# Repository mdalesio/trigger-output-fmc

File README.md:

# Trigger Output FMC

A single width HPC FMC board which provides 16 low jitter TTL outputs,
along with two Si5394 jitter cleaners with outputs connected to the MGTREF capable
when matched with the [LBL Marble](https://github.com/BerkeleyLab/Marble) FMC carrier.

This design is Open Hardware created by Osprey DCS and published under the terms of the
[CERN Open Hardware Licence Version 2 - Strongly Reciprocal](cern_ohl_s_v2.txt) license.

This repository contains KiCad 9.0.4 design files.

- [Data sheet](datasheet.md)
- [Current generated](https://osprey-dcs.github.io/trigger-output-fmc/)
  - [Schematic](https://osprey-dcs.github.io/trigger-output-fmc/trigger-output-fmc-schematic.pdf)
  - [BoM](https://osprey-dcs.github.io/trigger-output-fmc/trigger-output-fmc-bom.csv)
  - [STeP model](https://osprey-dcs.github.io/trigger-output-fmc/3D/trigger-output-fmc-3D.step)

## Block Diagram

## Status

Revision 1.0 produced and tested.

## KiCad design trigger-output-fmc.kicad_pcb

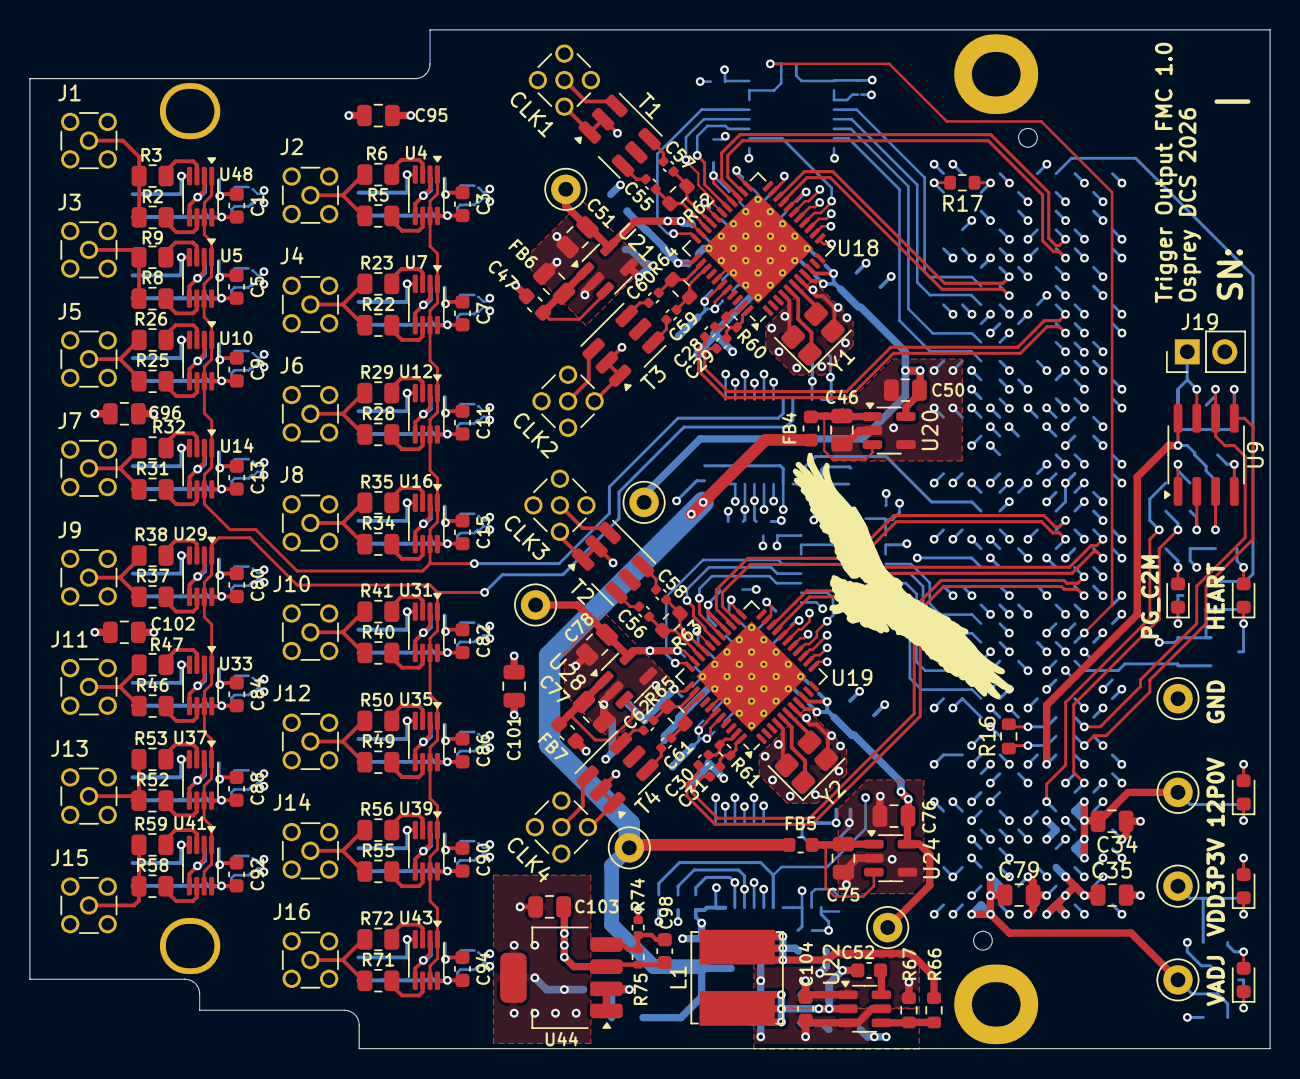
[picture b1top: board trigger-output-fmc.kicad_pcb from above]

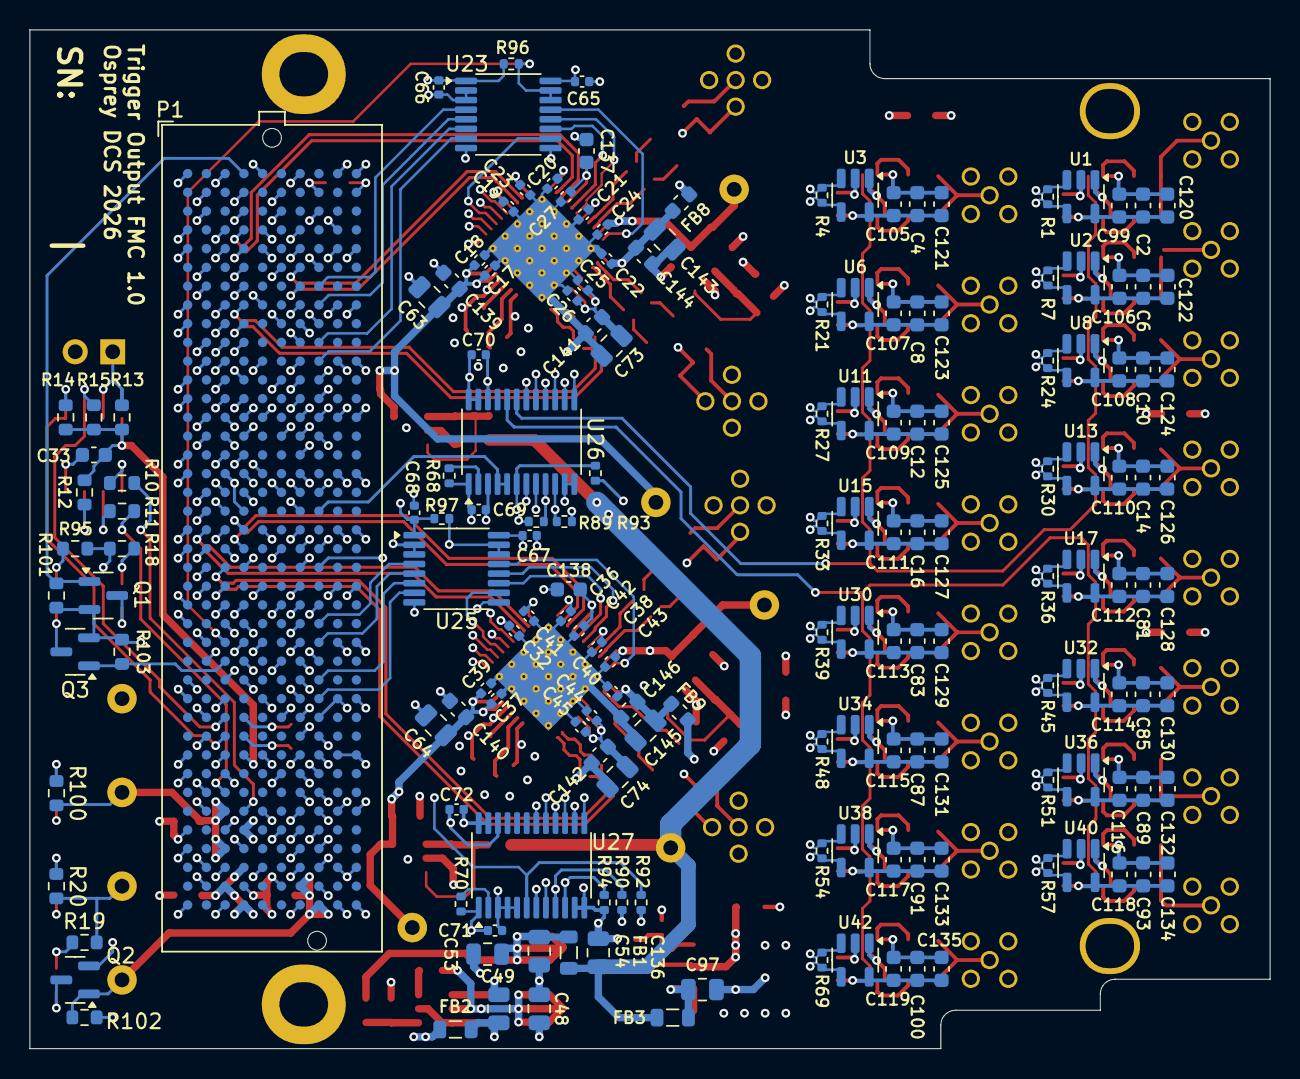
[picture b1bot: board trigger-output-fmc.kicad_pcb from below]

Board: 8 copper layers, 84.0 x 69.0 mm, 335 parts (168 on the bottom side), 226 nets.

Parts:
C1, C2, C3, C4, C5, C6, C7, C8, C9, C10, C11, C12, C13, C14, C15, C16, C52, C80, C81, C82, C83, C84, C85, C86, C87, C88, C89, C90, C91, C92, C93, C94, C100, C104: 100nF; C_0603_1608Metric
C17, C18, C19, C20, C21, C22, C23, C24, C25, C26, C27, C28, C29, C30, C31, C32, C36, C37, C38, C39, C40, C41, C42, C43, C44, C45, C55, C56, C57, C58, C59, C60, C61, C62, C65, C66, C67, C68, C69, C70, C71, C72: 100nF; C_0402_1005Metric
C33, C120, C121, C122, C123, C124, C125, C126, C127, C128, C129, C130, C131, C132, C133, C134, C135, C137, C138, C139, C140, C141, C142, C144, C146: 1uF; C_0603_1608Metric
C34, C35, C53, C54, C79, C136: 22uF; C_0805_2012Metric
C46, C47, C48, C49, C50, C51, C63, C64, C73, C74, C75, C76, C77, C78, C95, C96, C97, C101, C102, C103, C143, C145: 10uF; C_0805_2012Metric
C98: 62pF; C_0603_1608Metric
C99, C105, C106, C107, C108, C109, C110, C111, C112, C113, C114, C115, C116, C117, C118, C119: 10nF; C_0603_1608Metric
CLK1, CLK2, CLK3, CLK4: MMCX; MMCX_Molex_73415-1471_Vertical
D1, D2, D3, D4, D5: Green; LED_0603_1608Metric
FB1, FB2, FB3: 300@100MHz; L_0805_2012Metric
FB4, FB5, FB6, FB7, FB8, FB9: 120@100MHz; L_0603_1608Metric
H1, H2: MountingHole; MountingHole_3.0mm_M2.5_Pad_3.3mm_UniversalMarbleSlot
H3, H4: MountingHole; MountingHole_3.0mm_3.8mm_Pad_3.3mm_UniversalMarbleSlot
J1, J2, J3, J4, J5, J6, J7, J8, J9, J10, J11, J12, J13, J14, J15, J16: MMCX; MMCX_Molex_73415-1471_Vertical
J19: WP Jumper; PinHeader_1x02_P2.54mm_Vertical
L1: SRN6045TA-3R3Y; L_Bourns_SRN6045TA
Logo1: Osprey Logo; Logo_2X
P1: ASP-134488-01; Samtec_FMC_ASP-134602-01_10x40_P1.27mm_Vertical
Q1, Q2, Q3: FDN335N; SOT-23
R1, R4, R7, R21, R24, R27, R30, R33, R36, R39, R45, R48, R51, R54, R57, R60, R61, R69: 100R; R_0402_1005Metric
R2, R3, R5, R6, R8, R9, R22, R23, R25, R26, R28, R29, R31, R32, R34, R35, R37, R38, R40, R41, R46, R47, R49, R50, R52, R53, R55, R56, R58, R59, R71, R72: 88.7R; R_0805_2012Metric
R10, R11, R12, R14, R15: 4.75k; R_0603_1608Metric
R13: 11.5k; R_0603_1608Metric
R16, R17: 0R; R_0603_1608Metric
R18, R19, R20, R95: 1k; R_0603_1608Metric
R62, R63, R64, R65: 100R; R_0603_1608Metric
R66: 107k; R_0603_1608Metric
R67: 17.4k; R_0603_1608Metric
R68, R70, R89, R90, R91, R92, R93, R94, R96, R97: 4.75k; R_0402_1005Metric
R74: 18k; R_0402_1005Metric
R75: 56k; R_0402_1005Metric
R100: 8.2k; R_0603_1608Metric
R101, R102, R103: 100k; R_0603_1608Metric
T1, T2, T3, T4: TCM2-43X+; Mini-Circuits_DB1627_rounded_pads
TP1: Keystone5001; TestPoint_Keystone_5000-5004_Miniature
TP2, TP3, TP4, TP5, TP6, TP7, TP8, TP9: Keystone5000; TestPoint_Keystone_5000-5004_Miniature
U1, U2, U3, U6, U8, U11, U13, U15, U17, U30, U32, U34, U36, U38, U40, U42: TLV3601; SOT-23-5
U4, U5, U7, U10, U12, U14, U16, U29, U31, U33, U35, U37, U39, U41, U43, U48: SN74LVC2G126; VSSOP-8_2.3x2mm_P0.5mm
U9: AT24C64D; SOIC-8_3.9x4.9mm_P1.27mm
U18, U19: SI5394; QFN-44-1EP_7x7mm_P0.5mm_EP5.2x5.2mm_ThermalVias
U20, U24: TLV75733PDBV; SOT-23-5
U21, U28: TLV75718PDBV; SOT-23-5
U22: TPS563200; SOT-23-6
U23, U25: 74AVC4T245; TSSOP-16_4.4x5mm_P0.65mm
U26, U27: 74LVC8T245; TSSOP-24_4.4x7.8mm_P0.65mm
U44: LP3855EMP-ADJ/NOPB; SOT-223-5
Y1, Y2: CX3225SB48000D0FPJC1; Crystal_SMD_Abracon_ABM8AIG-4Pin_3.2x2.5mm

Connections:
3P3VAUX: C33.1, P1.D32, R12.1, R13.1, R14.1, R15.1, U9.8 (VCC)
+12V_FMC: C34.1, FB2.1, P1.C35, P1.C37, R100.2, TP2.1
/Digital IO/D_Output0.N: P1.G13, R1.2, U1.4 (-)
/Digital IO/D_Output0.P: P1.G12, R1.1, U1.3 (+)
/Digital IO/D_Output1.N: P1.H14, R4.2, U3.4 (-)
/Digital IO/D_Output1.P: P1.H13, R4.1, U3.3 (+)
/Digital IO/D_Output2.N: P1.G16, R7.2, U2.4 (-)
/Digital IO/D_Output2.P: P1.G15, R7.1, U2.3 (+)
/Digital IO/D_Output3.N: P1.D15, R21.2, U6.4 (-)
/Digital IO/D_Output3.P: P1.D14, R21.1, U6.3 (+)
/Digital IO/D_Output4.N: P1.C15, R24.2, U8.4 (-)
/Digital IO/D_Output4.P: P1.C14, R24.1, U8.3 (+)
/Digital IO/D_Output5.N: P1.G19, R27.2, U11.4 (-)
/Digital IO/D_Output5.P: P1.G18, R27.1, U11.3 (+)
/Digital IO/D_Output6.N: P1.D18, R30.2, U13.4 (-)
/Digital IO/D_Output6.P: P1.D17, R30.1, U13.3 (+)
/Digital IO/D_Output7.N: P1.C19, R33.2, U15.4 (-)
/Digital IO/D_Output7.P: P1.C18, R33.1, U15.3 (+)
/Digital IO/D_Output8.N: P1.G22, R36.2, U17.4 (-)
/Digital IO/D_Output8.P: P1.G21, R36.1, U17.3 (+)
/Digital IO/D_Output9.N: P1.G28, R39.2, U30.4 (-)
/Digital IO/D_Output9.P: P1.G27, R39.1, U30.3 (+)
/Digital IO/D_Output10.N: P1.G31, R45.2, U32.4 (-)
/Digital IO/D_Output10.P: P1.G30, R45.1, U32.3 (+)
/Digital IO/D_Output11.N: P1.H32, R48.2, U34.4 (-)
/Digital IO/D_Output11.P: P1.H31, R48.1, U34.3 (+)
/Digital IO/D_Output12.N: P1.G34, R51.2, U36.4 (-)
/Digital IO/D_Output12.P: P1.G33, R51.1, U36.3 (+)
/Digital IO/D_Output13.N: P1.H35, R54.2, U38.4 (-)
/Digital IO/D_Output13.P: P1.H34, R54.1, U38.3 (+)
/Digital IO/D_Output14.N: P1.H38, R57.2, U40.4 (-)
/Digital IO/D_Output14.P: P1.H37, R57.1, U40.3 (+)
/Digital IO/D_Output15.N: P1.G37, R69.2, U42.4 (-)
/Digital IO/D_Output15.P: P1.G36, R69.1, U42.3 (+)
/Digital IO/OE_A: U4.1 (1OE), U4.7 (2OE), U5.1 (1OE), U5.7 (2OE), U7.1 (1OE), U7.7 (2OE), U10.1 (1OE), U10.7 (2OE), U12.1 (1OE), U12.7 (2OE), U14.1 (1OE), U14.7 (2OE), U16.1 (1OE), U16.7 (2OE), U26.19 (B3), U48.1 (1OE), U48.7 (2OE)
/Digital IO/OE_B: U26.20 (B2), U29.1 (1OE), U29.7 (2OE), U31.1 (1OE), U31.7 (2OE), U33.1 (1OE), U33.7 (2OE), U35.1 (1OE), U35.7 (2OE), U37.1 (1OE), U37.7 (2OE), U39.1 (1OE), U39.7 (2OE), U41.1 (1OE), U41.7 (2OE), U43.1 (1OE), U43.7 (2OE)
/Digital IO/Switched_5P45V: C136.1, FB1.2, FB3.1, FB4.1, FB5.1, TP8.1
/Digital IO/VCC: C1.2, C2.2, C3.2, C4.2, C5.2, C6.2, C7.2, C8.2, C9.2, C10.2, C11.2, C12.2, C13.2, C14.2, C15.2, C16.2, C80.2, C81.2, C82.2, C83.2, C84.2, C85.2, C86.2, C87.2, C88.2, C89.2, C90.2, C91.2, C92.2, C93.2, C94.2, C95.1, C96.1, C98.1, C99.2, C100.2, C101.1, C102.1, C103.1, C105.2, C106.2, C107.2, C108.2, C109.2, C110.2, C111.2, C112.2, C113.2, C114.2, C115.2, C116.2, C117.2, C118.2, C119.2, C120.2, C121.2, C122.2, C123.2, C124.2, C125.2, C126.2, C127.2, C128.2, C129.2, C130.2, C131.2, C132.2, C133.2, C134.2, C135.2, R75.2, U1.5 (V+), U2.5 (V+), U3.5 (V+), U4.8 (V_{CC}), U5.8 (V_{CC}), U6.5 (V+), U7.8 (V_{CC}), U8.5 (V+), U10.8 (V_{CC}), U11.5 (V+), U12.8 (V_{CC}), U13.5 (V+), U14.8 (V_{CC}), U15.5 (V+), U16.8 (V_{CC}), U17.5 (V+), U29.8 (V_{CC}), U30.5 (V+), U31.8 (V_{CC}), U32.5 (V+), U33.8 (V_{CC}), U34.5 (V+), U35.8 (V_{CC}), U36.5 (V+), U37.8 (V_{CC}), U38.5 (V+), U39.8 (V_{CC}), U40.5 (V+), U41.8 (V_{CC}), U42.5 (V+), U43.8 (V_{CC}), U44.3 (Vout), U48.8 (V_{CC})
/Digital IO/out_buffer0/Out: J1.1 (In), R2.2, R3.2
/Digital IO/out_buffer1/Out: J2.1 (In), R5.2, R6.2
/Digital IO/out_buffer2/Out: J3.1 (In), R8.2, R9.2
/Digital IO/out_buffer3/Out: J4.1 (In), R22.2, R23.2
/Digital IO/out_buffer4/Out: J5.1 (In), R25.2, R26.2
/Digital IO/out_buffer5/Out: J6.1 (In), R28.2, R29.2
/Digital IO/out_buffer6/Out: J7.1 (In), R31.2, R32.2
/Digital IO/out_buffer7/Out: J8.1 (In), R34.2, R35.2
/Digital IO/out_buffer8/Out: J9.1 (In), R37.2, R38.2
/Digital IO/out_buffer9/Out: J10.1 (In), R40.2, R41.2
/Digital IO/out_buffer10/Out: J11.1 (In), R46.2, R47.2
/Digital IO/out_buffer11/Out: J12.1 (In), R49.2, R50.2
/Digital IO/out_buffer12/Out: J13.1 (In), R52.2, R53.2
/Digital IO/out_buffer13/Out: J14.1 (In), R55.2, R56.2
/Digital IO/out_buffer14/Out: J15.1 (In), R58.2, R59.2
/Digital IO/out_buffer15/Out: J16.1 (In), R71.2, R72.2
/FMC/Cleaned_CLK_0.N: P1.G7, U18.19 (~OUT0)
/FMC/Cleaned_CLK_0.P: P1.G6, U18.20 (Out0)
/FMC/Cleaned_CLK_1.N: P1.D21, U19.24 (~OUT1)
/FMC/Cleaned_CLK_1.P: P1.D20, U19.25 (Out1)
/FMC/Cleaner_Fault_0.INTR: P1.H7, U23.4 (A1)
/FMC/Cleaner_Fault_0.LOL: P1.H10, U23.6 (A3)
/FMC/Cleaner_Fault_0.LOS_XO: P1.H8, U23.5 (A2)
/FMC/Cleaner_Fault_1.INTR: P1.H25, U25.4 (A1)
/FMC/Cleaner_Fault_1.LOL: P1.H28, U25.6 (A3)
/FMC/Cleaner_Fault_1.LOS_XO: P1.H26, U25.5 (A2)
/FMC/Cleaner_SPI_0.CLK: P1.C10, U26.8 (A6)
/FMC/Cleaner_SPI_0.CS: P1.G10, R89.1, U26.9 (A7)
/FMC/Cleaner_SPI_0.OE: P1.D12, R91.1, U26.6 (A4)
/FMC/Cleaner_SPI_0.SDI: P1.C11, U26.7 (A5)
/FMC/Cleaner_SPI_0.SDO: P1.H11, U23.7 (A4)
/FMC/Cleaner_SPI_1.CLK: P1.D24, U27.8 (A6)
/FMC/Cleaner_SPI_1.CS: P1.G25, R90.1, U27.9 (A7)
/FMC/Cleaner_SPI_1.OE: P1.D27, R92.1, U27.6 (A4)
/FMC/Cleaner_SPI_1.SDI: P1.D26, U27.7 (A5)
/FMC/Cleaner_SPI_1.SDO: P1.H29, U25.7 (A4)
/FMC/Cleaner_~OE_0: P1.C26, R96.1, U23.14 (OE), U23.15 (OE)
/FMC/Cleaner_~OE_1: P1.H22, R97.1, U25.14 (OE), U25.15 (OE)
/FMC/Cleaner_~RST_0: P1.G9, R93.2, U26.10 (A8)
/FMC/Cleaner_~RST_1: P1.G24, R94.2, U27.10 (A8)
/FMC/EEPROM_GA0: P1.C34, R11.1
/FMC/EEPROM_GA1: P1.D35, R10.1
/FMC/EEPROM_SCL: P1.C30, R15.2, U9.6 (SCL)
/FMC/EEPROM_SDA: P1.C31, R14.2, U9.5 (SDA)
/FMC/FMC_GBTCLK0.N: P1.D5, U18.24 (~OUT1)
/FMC/FMC_GBTCLK0.P: P1.D4, U18.25 (Out1)
/FMC/FMC_GBTCLK1.N: P1.B21, U19.19 (~OUT0)
/FMC/FMC_GBTCLK1.P: P1.B20, U19.20 (Out0)
/FMC/OE_Digital_Outputs: P1.H19, U26.4 (A2), U26.5 (A3)
/FMC/Recovered_CLK_0.N: C29.1, P1.D8
/FMC/Recovered_CLK_0.P: C28.1, P1.D9
/FMC/Recovered_CLK_1.N: C31.1, P1.C22
/FMC/Recovered_CLK_1.P: C30.1, P1.C23
/Jitter Cleaner0/Cleaned_CLK2.N: C57.1, R62.2, U18.30 (~OUT2)
/Jitter Cleaner0/Cleaned_CLK2.P: C55.1, R62.1, U18.31 (Out2)
/Jitter Cleaner0/Cleaned_CLK3.N: C60.1, R64.2, U18.35 (~OUT3)
/Jitter Cleaner0/Cleaned_CLK3.P: C59.1, R64.1, U18.36 (Out3)
/Jitter Cleaner0/Control.INTR: U18.33 (~INTR), U23.13 (B1)
/Jitter Cleaner0/Control.LOL: U18.27 (~LOL), U23.11 (B3)
/Jitter Cleaner0/Control.LOS_XO: U18.28 (~LOS_XAXB), U23.12 (B2)
/Jitter Cleaner0/Control.OE: U18.12 (~OE), U26.18 (B4)
/Jitter Cleaner0/Control.RST: U18.17 (~RST), U26.14 (B8)
/Jitter Cleaner0/Control.SPI_CLK: U18.14 (SCLK), U26.16 (B6)
/Jitter Cleaner0/Control.SPI_CS: U18.16 (A0/~CS), U26.15 (B7)
/Jitter Cleaner0/Control.SPI_SDI: U18.13 (SDA/SDIO), U26.17 (B5)
/Jitter Cleaner0/Control.SPI_SDO: U18.15 (A1/SDO), U23.10 (B4)
/Jitter Cleaner0/In0.N: C29.2, R60.2, U18.44 (~IN0)
/Jitter Cleaner0/In0.P: C28.2, R60.1, U18.43 (In0)
/Jitter Cleaner0/VDD: C23.1, C24.1, C25.1, C26.1, C51.1, C73.1, C141.1, TP5.1, U18.21 (VDD), U18.32 (VDD), U18.39 (VDD), U18.40 (VDD), U21.5 (OUT)
/Jitter Cleaner0/VDDA: C17.1, C18.1, C50.1, C63.1, C139.1, TP7.1, U18.8 (VDDA), U18.9 (VDDA), U20.5 (OUT)
/Jitter Cleaner1/Cleaned_CLK2.N: C58.1, R63.2, U19.30 (~OUT2)
/Jitter Cleaner1/Cleaned_CLK2.P: C56.1, R63.1, U19.31 (Out2)
/Jitter Cleaner1/Cleaned_CLK3.N: C62.1, R65.2, U19.35 (~OUT3)
/Jitter Cleaner1/Cleaned_CLK3.P: C61.1, R65.1, U19.36 (Out3)
/Jitter Cleaner1/Control.INTR: U19.33 (~INTR), U25.13 (B1)
/Jitter Cleaner1/Control.LOL: U19.27 (~LOL), U25.11 (B3)
/Jitter Cleaner1/Control.LOS_XO: U19.28 (~LOS_XAXB), U25.12 (B2)
/Jitter Cleaner1/Control.OE: U19.12 (~OE), U27.18 (B4)
/Jitter Cleaner1/Control.RST: U19.17 (~RST), U27.14 (B8)
/Jitter Cleaner1/Control.SPI_CLK: U19.14 (SCLK), U27.16 (B6)
/Jitter Cleaner1/Control.SPI_CS: U19.16 (A0/~CS), U27.15 (B7)
/Jitter Cleaner1/Control.SPI_SDI: U19.13 (SDA/SDIO), U27.17 (B5)
/Jitter Cleaner1/Control.SPI_SDO: U19.15 (A1/SDO), U25.10 (B4)
/Jitter Cleaner1/In0.N: C31.2, R61.2, U19.44 (~IN0)
/Jitter Cleaner1/In0.P: C30.2, R61.1, U19.43 (In0)
/Jitter Cleaner1/VDD: C41.1, C43.1, C44.1, C45.1, C74.1, C78.1, C142.1, TP9.1, U19.21 (VDD), U19.32 (VDD), U19.39 (VDD), U19.40 (VDD), U28.5 (OUT)
/Jitter Cleaner1/VDDA: C37.1, C39.1, C64.1, C76.1, C140.1, TP6.1, U19.8 (VDDA), U19.9 (VDDA), U24.5 (OUT)
GND: C1.1, C2.1, C3.1, C4.1, C5.1, C6.1, C7.1, C8.1, C9.1, C10.1, C11.1, C12.1, C13.1, C14.1, C15.1, C16.1, C17.2, C18.2, C19.2, C20.2, C21.2, C22.2, C23.2, C24.2, C25.2, C26.2, C27.2, C32.2, C33.2, C34.2, C35.2, C36.2, C37.2, C38.2, C39.2, C40.2, C41.2, C42.2, C43.2, C44.2, C45.2, C46.2, C47.2, C48.2, C49.2, C50.2, C51.2, C53.2, C54.2, C63.2, C64.2, C65.1, C66.1, C67.1, C68.1, C69.1, C70.1, C71.1, C72.1, C73.2, C74.2, C75.2, C76.2, C77.2, C78.2, C79.2, C80.1, C81.1, C82.1, C83.1, C84.1, C85.1, C86.1, C87.1, C88.1, C89.1, C90.1, C91.1, C92.1, C93.1, C94.1, C95.2, C96.2, C97.2, C99.1, C100.1, C101.2, C102.2, C103.2, C104.1, C105.1, C106.1, C107.1, C108.1, C109.1, C110.1, C111.1, C112.1, C113.1, C114.1, C115.1, C116.1, C117.1, C118.1, C119.1, C120.1, C121.1, C122.1, C123.1, C124.1, C125.1, C126.1, C127.1, C128.1, C129.1, C130.1, C131.1, C132.1, C133.1, C134.1, C135.1, C136.2, C137.2, C138.2, C139.2, C140.2, C141.2, C142.2, C143.2, C144.2, C145.2, C146.2, CLK1.2 (Ext), CLK2.2 (Ext), CLK3.2 (Ext), CLK4.2 (Ext), D3.1 (K), D5.1 (K), H1.1, H2.1, H3.1, H4.1, J1.2 (Ext), J2.2 (Ext), J3.2 (Ext), J4.2 (Ext), J5.2 (Ext), J6.2 (Ext), J7.2 (Ext), J8.2 (Ext), J9.2 (Ext), J10.2 (Ext), J11.2 (Ext), J12.2 (Ext), J13.2 (Ext), J14.2 (Ext), J15.2 (Ext), J16.2 (Ext), J19.2, P1.A1, P1.A4, P1.A5, P1.A8, P1.A9, P1.A12, P1.A13, P1.A16, P1.A17, P1.A20, P1.A21, P1.A24, P1.A25, P1.A28, P1.A29, P1.A32, P1.A33, P1.A36, P1.A37, P1.A40, P1.B2, P1.B3, P1.B6, P1.B7, P1.B10, P1.B11, P1.B14, P1.B15, P1.B18, P1.B19, P1.B22, P1.B23, P1.B26, P1.B27, P1.B30, P1.B31, P1.B34, P1.B35, P1.B38, P1.B39, P1.C1, P1.C4, P1.C5, P1.C8, P1.C9, P1.C12, P1.C13, P1.C16, P1.C17, P1.C20, P1.C21, P1.C24, P1.C25, P1.C28, P1.C29, P1.C32, P1.C33, P1.C36, P1.C38, P1.C40, P1.D2, P1.D3, P1.D6, P1.D7, P1.D10, P1.D13, P1.D16, P1.D19, P1.D22, P1.D25, P1.D28, P1.D37, P1.D39, P1.E1, P1.E4, P1.E5, P1.E8, P1.E11, P1.E14, P1.E17, P1.E20, P1.E23, P1.E26, P1.E29, P1.E32, P1.E35, P1.E38, P1.E40, P1.F2, P1.F3, P1.F6, P1.F9, P1.F12, P1.F15, P1.F18, P1.F21, P1.F24, P1.F27, P1.F30, P1.F33, P1.F36, P1.F39, P1.G1, P1.G4, P1.G5, P1.G8, P1.G11, P1.G14, P1.G17, P1.G20, P1.G23, P1.G26, P1.G29, P1.G32, P1.G35, P1.G38, P1.G40, P1.H3, P1.H6, P1.H9, P1.H12, P1.H15, P1.H18, P1.H21, P1.H24, P1.H27, P1.H30, P1.H33, P1.H36, P1.H39, P1.J1, P1.J4, P1.J5, P1.J8, P1.J11, P1.J14, P1.J17, P1.J20, P1.J23, P1.J26, P1.J29, P1.J32, P1.J35, P1.J38 (J39), P1.J40, P1.K1, P1.K2, P1.K5, P1.K8, P1.K11, P1.K14, P1.K17, P1.K20, P1.K23, P1.K26, P1.K29, P1.K32, P1.K35, P1.K38, P1.K40, Q1.2 (S), Q2.2 (S), Q3.2 (S), R17.2, R67.2, R74.1, R93.1, R94.1, R101.1, R102.1, R103.1, T1.1 (PRI), T1.2 (PRI), T2.1 (PRI), T2.2 (PRI), T3.1 (PRI), T3.2 (PRI), T4.1 (PRI), T4.2 (PRI), TP1.1, U1.2 (V-), U2.2 (V-), U3.2 (V-), U4.4 (GND), U5.4 (GND), U6.2 (V-), U7.4 (GND), U8.2 (V-), U9.4 (GND), U10.4 (GND), U11.2 (V-), U12.4 (GND), U13.2 (V-), U14.4 (GND), U15.2 (V-), U16.4 (GND), U17.2 (V-), U18.38 (I2C_SEL), U18.45 (GND_PAD), U19.38 (I2C_SEL), U19.45 (GND_PAD), U20.2 (GND), U20.4 (NC), U21.2 (GND), U21.4 (NC), U22.1 (GND), U23.2 (1DIR), U23.3 (2DIR), U23.8 (GND), U23.9 (GND), U24.2 (GND), U24.4 (NC), U25.2 (1DIR), U25.3 (2DIR), U25.8 (GND), U25.9 (GND), U26.3 (A1), U26.11 (GND), U26.12 (GND), U26.13 (GND), U26.22 (OE), U27.3 (A1), U27.4 (A2), U27.5 (A3), U27.11 (GND), U27.12 (GND), U27.13 (GND), U27.22 (OE), U28.2 (GND), U28.4 (NC), U29.4 (GND), U30.2 (V-), U31.4 (GND), U32.2 (V-), U33.4 (GND), U34.2 (V-), U35.4 (GND), U36.2 (V-), U37.4 (GND), U38.2 (V-), U39.4 (GND), U40.2 (V-), U41.4 (GND), U42.2 (V-), U43.4 (GND), U44.5 (GND), U48.4 (GND)
Heartbeat_LED: P1.C27, Q3.1 (G), R103.2
unnamed: C53.1, C54.1, FB1.1, L1.2, R66.1
unnamed: CLK1.1 (In), T1.3 (PRI_DOT)
unnamed: CLK2.1 (In), T3.3 (PRI_DOT)
unnamed: CLK3.1 (In), T2.3 (PRI_DOT)
unnamed: CLK4.1 (In), T4.3 (PRI_DOT)
unnamed: D1.2 (A), R18.1
unnamed: D1.1 (K), Q1.3 (D)
unnamed: D2.2 (A), R19.1
unnamed: D2.1 (K), Q2.3 (D)
unnamed: D3.2 (A), R20.1
unnamed: D4.2 (A), R95.1
unnamed: D4.1 (K), Q3.3 (D)
unnamed: D5.2 (A), R100.1
unnamed: J19.1, R13.2, U9.7 (WP)
unnamed: C57.2, T1.4 (SEC)
unnamed: C55.2, T1.6 (SEC_DOT)
unnamed: C58.2, T2.4 (SEC)
unnamed: C56.2, T2.6 (SEC_DOT)
unnamed: C60.2, T3.4 (SEC)
unnamed: C59.2, T3.6 (SEC_DOT)
unnamed: C62.2, T4.4 (SEC)
unnamed: C61.2, T4.6 (SEC_DOT)
unnamed: U3.1, U4.2 (1A), U4.5 (2A)
unnamed: R5.1, U4.6 (1Y)
unnamed: R6.1, U4.3 (2Y)
unnamed: U2.1, U5.2 (1A), U5.5 (2A)
unnamed: R8.1, U5.6 (1Y)
unnamed: R9.1, U5.3 (2Y)
unnamed: U6.1, U7.2 (1A), U7.5 (2A)
unnamed: R22.1, U7.6 (1Y)
unnamed: R23.1, U7.3 (2Y)
unnamed: R10.2, U9.1 (A0)
unnamed: R11.2, U9.2 (A1)
unnamed: R12.2, U9.3 (A2)
unnamed: U8.1, U10.2 (1A), U10.5 (2A)
unnamed: R25.1, U10.6 (1Y)
unnamed: R26.1, U10.3 (2Y)
unnamed: U11.1, U12.2 (1A), U12.5 (2A)
unnamed: R28.1, U12.6 (1Y)
unnamed: R29.1, U12.3 (2Y)
unnamed: U13.1, U14.2 (1A), U14.5 (2A)
unnamed: R31.1, U14.6 (1Y)
unnamed: R32.1, U14.3 (2Y)
unnamed: U15.1, U16.2 (1A), U16.5 (2A)
unnamed: R34.1, U16.6 (1Y)
unnamed: R35.1, U16.3 (2Y)
unnamed: C19.1, C20.1, C21.1, C22.1, C143.1, C144.1, FB8.2, U18.18 (VDDO0), U18.23 (VDDO1), U18.29 (VDDO2), U18.34 (VDDO3)
unnamed: U18.4 (X1), U18.7 (X2), Y1.2, Y1.4
unnamed: U18.5 (XA), Y1.1
unnamed: U18.6 (XB), Y1.3
unnamed: C32.1, C36.1, C38.1, C40.1, C145.1, C146.1, FB9.2, U19.18 (VDDO0), U19.23 (VDDO1), U19.29 (VDDO2), U19.34 (VDDO3)
unnamed: U19.4 (X1), U19.7 (X2), Y2.2, Y2.4
unnamed: U19.5 (XA), Y2.1
unnamed: U19.6 (XB), Y2.3
unnamed: C46.1, FB4.2, U20.1 (IN), U20.3 (EN)
unnamed: C47.1, FB6.2, U21.1 (IN), U21.3 (EN)
unnamed: C48.1, C49.1, C104.2, FB2.2, U22.3 (VIN), U22.5 (EN)
unnamed: C52.2, L1.1, U22.2 (SW)
unnamed: C52.1, U22.6 (VBST)
unnamed: R66.2, R67.1, U22.4 (VFB)
unnamed: C75.1, FB5.2, U24.1 (IN), U24.3 (EN)
unnamed: R68.1, U26.2 (DIR)
unnamed: R70.1, U27.2 (DIR)
unnamed: C77.1, FB7.2, U28.1 (IN), U28.3 (EN)
unnamed: U17.1, U29.2 (1A), U29.5 (2A)
unnamed: R37.1, U29.6 (1Y)
unnamed: R38.1, U29.3 (2Y)
unnamed: U30.1, U31.2 (1A), U31.5 (2A)
unnamed: R40.1, U31.6 (1Y)
unnamed: R41.1, U31.3 (2Y)
unnamed: U32.1, U33.2 (1A), U33.5 (2A)
unnamed: R46.1, U33.6 (1Y)
unnamed: R47.1, U33.3 (2Y)
unnamed: U34.1, U35.2 (1A), U35.5 (2A)
unnamed: R49.1, U35.6 (1Y)
unnamed: R50.1, U35.3 (2Y)
unnamed: U36.1, U37.2 (1A), U37.5 (2A)
unnamed: R52.1, U37.6 (1Y)
unnamed: R53.1, U37.3 (2Y)
unnamed: U38.1, U39.2 (1A), U39.5 (2A)
unnamed: R55.1, U39.6 (1Y)
unnamed: R56.1, U39.3 (2Y)
unnamed: U40.1, U41.2 (1A), U41.5 (2A)
unnamed: R58.1, U41.6 (1Y)
unnamed: R59.1, U41.3 (2Y)
unnamed: U42.1, U43.2 (1A), U43.5 (2A)
unnamed: R71.1, U43.6 (1Y)
unnamed: R72.1, U43.3 (2Y)
unnamed: C98.2, R74.2, R75.1, U44.4 (ADJ)
unnamed: C97.1, FB3.2, U44.1 (~SD), U44.2 (Vin)
unnamed: U1.1, U48.2 (1A), U48.5 (2A)
unnamed: R2.1, U48.6 (1Y)
unnamed: R3.1, U48.3 (2Y)
PG_C2M: P1.D1, Q1.1 (G), R101.2
PRSNT: P1.H2, R17.1
TDI: P1.D30, R16.2
TDO: P1.D31, R16.1
VADJ: C66.2, C68.2, C69.2, C71.2, C79.1, FB8.1, FB9.1, P1.G39, P1.H40, Q2.1 (G), R68.2, R70.2, R89.2, R90.2, R91.2, R92.2, R96.2, R97.2, R102.2, TP4.1, U23.1 (VCCA), U25.1 (VCCA), U26.1 (VCCA), U27.1 (VCCA)
VDD3P3V: C27.1, C35.1, C42.1, C65.2, C67.2, C70.2, C72.2, C137.1, C138.1, FB6.1, FB7.1, P1.C39, P1.D36, P1.D38, P1.D40, R18.2, R19.2, R20.2, R95.2, TP3.1, U18.26 (VDDS), U19.26 (VDDS), U23.16 (VCCB), U25.16 (VCCB), U26.23 (VCCB), U26.24 (VCCB), U27.23 (VCCB), U27.24 (VCCB)

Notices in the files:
trigger-output-fmc.kicad_pcb:
SPDX-FileCopyrightText: 2025 Osprey DCS
SPDX-License-Identifier: CERN-OHL-S-2.0+
